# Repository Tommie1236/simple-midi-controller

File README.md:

# Simple MIDI Controller

### A simple 32-button MIDI controller with bank support, built around the RP2040 microcontroller (e.g., RP2040-Zero, but other RP2040 boards should work with appropriate pin changes). Designed for compatibility with any software that accepts USB MIDI input.
## Features

  32 configurable buttons
  Multiple banks for expanded control
  USB MIDI device class (works out-of-the-box with most DAWs and lighting control software)
  MAX7219 7-segment display for bank number
  LVGL graphics library integration for future graphical display support
  Example use: MyDMX, generic macropad for other MIDI-compatible software

## Hardware

  Primary target: RP2040-Zero
  Any RP2040-based board can be used (adjust pin mappings as needed)
  Wiring and assembly instructions: TODO!!

## Software Dependencies

  Raspberry Pi Pico SDK
  TinyUSB
  LVGL v9.4.0 (Light and Versatile Graphics Library)

## Building and Flashing

  Clone this repository and its dependencies.
  Build the firmware using the included build script in the root directory. 
  Optionally use the -l flag to automaticly use picotool to load it to the device.
  Or reboot into bootsel mode and drag the compiled binary(.uf2) onto the usb mass storage device. 

## Usage

Once flashed, the controller will appear as a standard USB MIDI device. It should work with any MIDI-compatible software. Currently tested with MyDMX, but suitable for general MIDI macro control.

For information about the LVGL graphics library integration, see [Code/LVGL_INTEGRATION.md](Code/LVGL_INTEGRATION.md).

Pin Configuration

  Default pin mappings are defined in the code for RP2040-Zero.
  If you use a different RP2040 board, update the pin definitions as needed in the source files.

## Roadmap

  - [x] implement segment display
  - [x] add banking support
  - [x] add LVGL graphics library for future graphical display/menu support
  - [ ] add a menu for configuration?
  - [ ] Add full hardware assembly and wiring instructions
  - [x] create pcb for easier replication without the big amount of soldering perfboard requires.
  - [x] ^ also schematic?
  
## Ai useage (hackclub Summer of Making)
I've used ai in this project. for example to create a base for this readme but i have also used some chatbots with high level debugging if i got stuck.
I've also had copilot enable in vscode when i started the project. but i've since switched to neovim and didn't add any ai or lsp yet. so mostly just high level debugging and writing text. (I'm very bad at this as you can probably already see.)
I really don't like using ai to generate code snippets. sometimes copilot is usefull when you need a lot of repeating code with just a simple parameter changing. But the rest of the time it is pretty useless imo and things like chatgpt/gemini make too many mistakes or inefficiencies to be usefull for snippets.

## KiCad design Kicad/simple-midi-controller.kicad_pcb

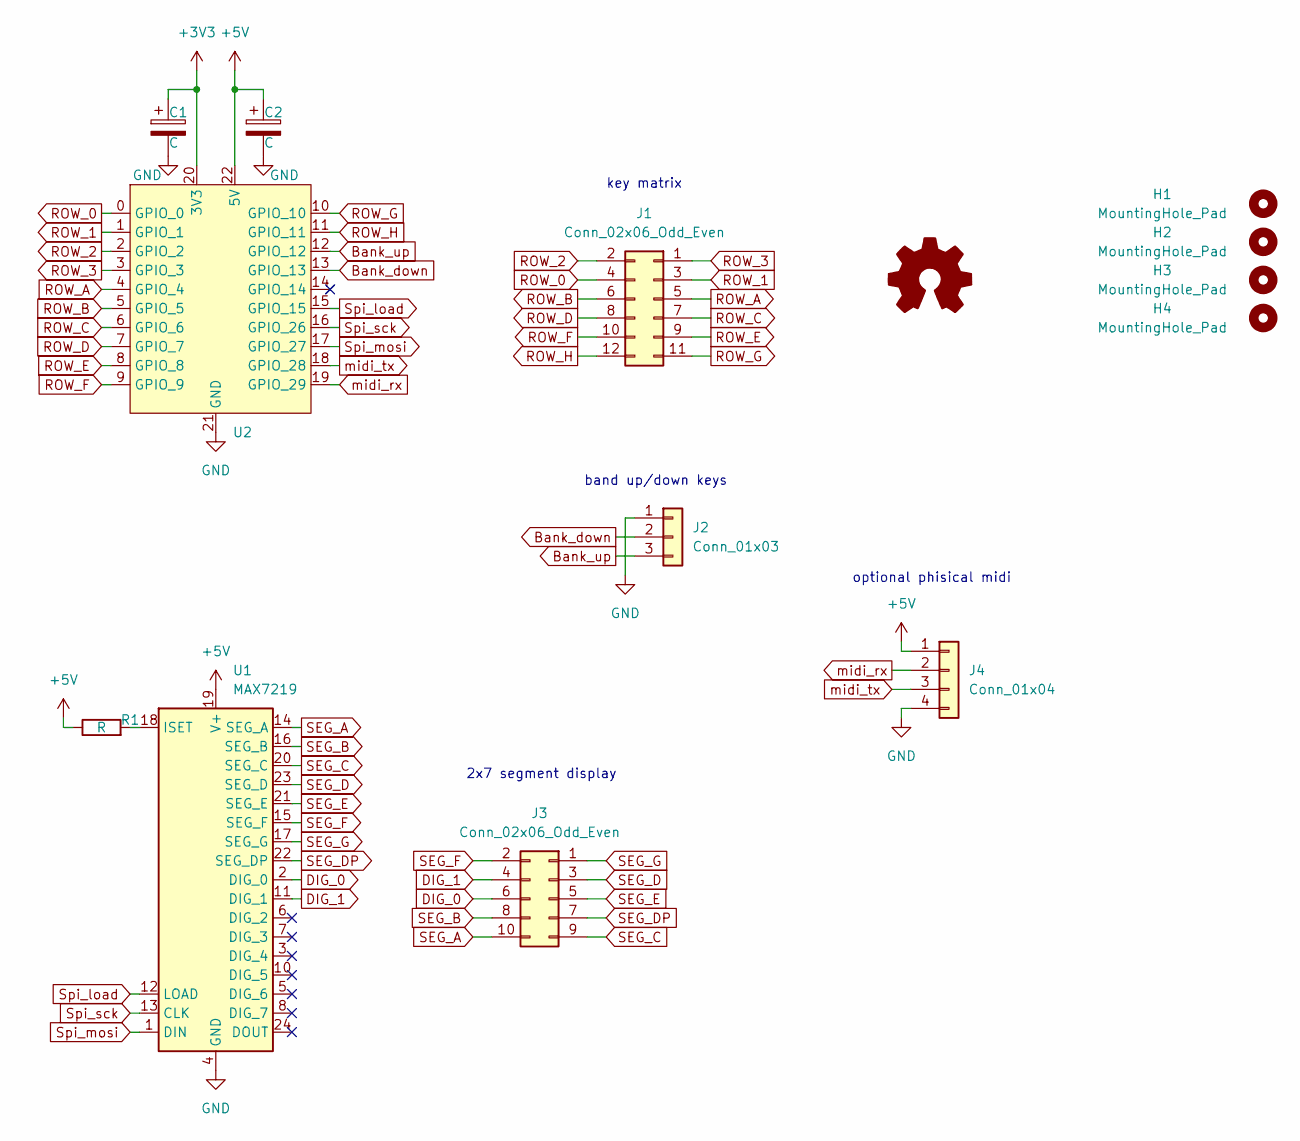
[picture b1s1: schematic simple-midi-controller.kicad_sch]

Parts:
C1, C2: C; CP_Radial_D5.0mm_P2.50mm
H1, H2, H3, H4: MountingHole_Pad; MountingHole_3.2mm_M3
J1: Conn_02x06_Odd_Even; PinHeader_2x06_P2.54mm_Vertical
J2: Conn_01x03; PinHeader_1x03_P2.54mm_Vertical
J3: Conn_02x06_Odd_Even; PinHeader_2x05_P2.54mm_Vertical
J4: Conn_01x04; PinHeader_1x04_P2.54mm_Vertical
R1: R; R_Axial_DIN0207_L6.3mm_D2.5mm_P10.16mm_Horizontal
U1: MAX7219; DIP-24_W7.62mm_Socket
U2: RP2040-Zero

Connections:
+3V3: C1.1, U2.20 (3V3)
+5V: C2.1, J4.1, R1.1, U1.19 (V+), U2.22 (5V)
Bank_down: J2.2, U2.13 (GPIO_13)
Bank_up: J2.3, U2.12 (GPIO_12)
DIG_0: J3.6, U1.2 (DIG_0)
DIG_1: J3.4, U1.11 (DIG_1)
GND: C1.2, C2.2, J2.1, J4.4, U1.4 (GND), U1.9 (GND), U2.21 (GND)
unnamed: R1.2, U1.18 (ISET)
ROW_0: J1.4, U2.0 (GPIO_0)
ROW_1: J1.3, U2.1 (GPIO_1)
ROW_2: J1.2, U2.2 (GPIO_2)
ROW_3: J1.1, U2.3 (GPIO_3)
ROW_A: J1.5, U2.4 (GPIO_4)
ROW_B: J1.6, U2.5 (GPIO_5)
ROW_C: J1.7, U2.6 (GPIO_6)
ROW_D: J1.8, U2.7 (GPIO_7)
ROW_E: J1.9, U2.8 (GPIO_8)
ROW_F: J1.10, U2.9 (GPIO_9)
ROW_G: J1.11, U2.10 (GPIO_10)
ROW_H: J1.12, U2.11 (GPIO_11)
SEG_A: J3.10, U1.14 (SEG_A)
SEG_B: J3.8, U1.16 (SEG_B)
SEG_C: J3.9, U1.20 (SEG_C)
SEG_D: J3.3, U1.23 (SEG_D)
SEG_DP: J3.7, U1.22 (SEG_DP)
SEG_E: J3.5, U1.21 (SEG_E)
SEG_F: J3.2, U1.15 (SEG_F)
SEG_G: J3.1, U1.17 (SEG_G)
Spi_load: U1.12 (LOAD), U2.15 (GPIO_15)
Spi_mosi: U1.1 (DIN), U2.17 (GPIO_27)
Spi_sck: U1.13 (CLK), U2.16 (GPIO_26)
midi_rx: J4.2, U2.19 (GPIO_29)
midi_tx: J4.3, U2.18 (GPIO_28)

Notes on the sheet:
2x7 segment display
optional phisical midi
band up/down keys
key matrix

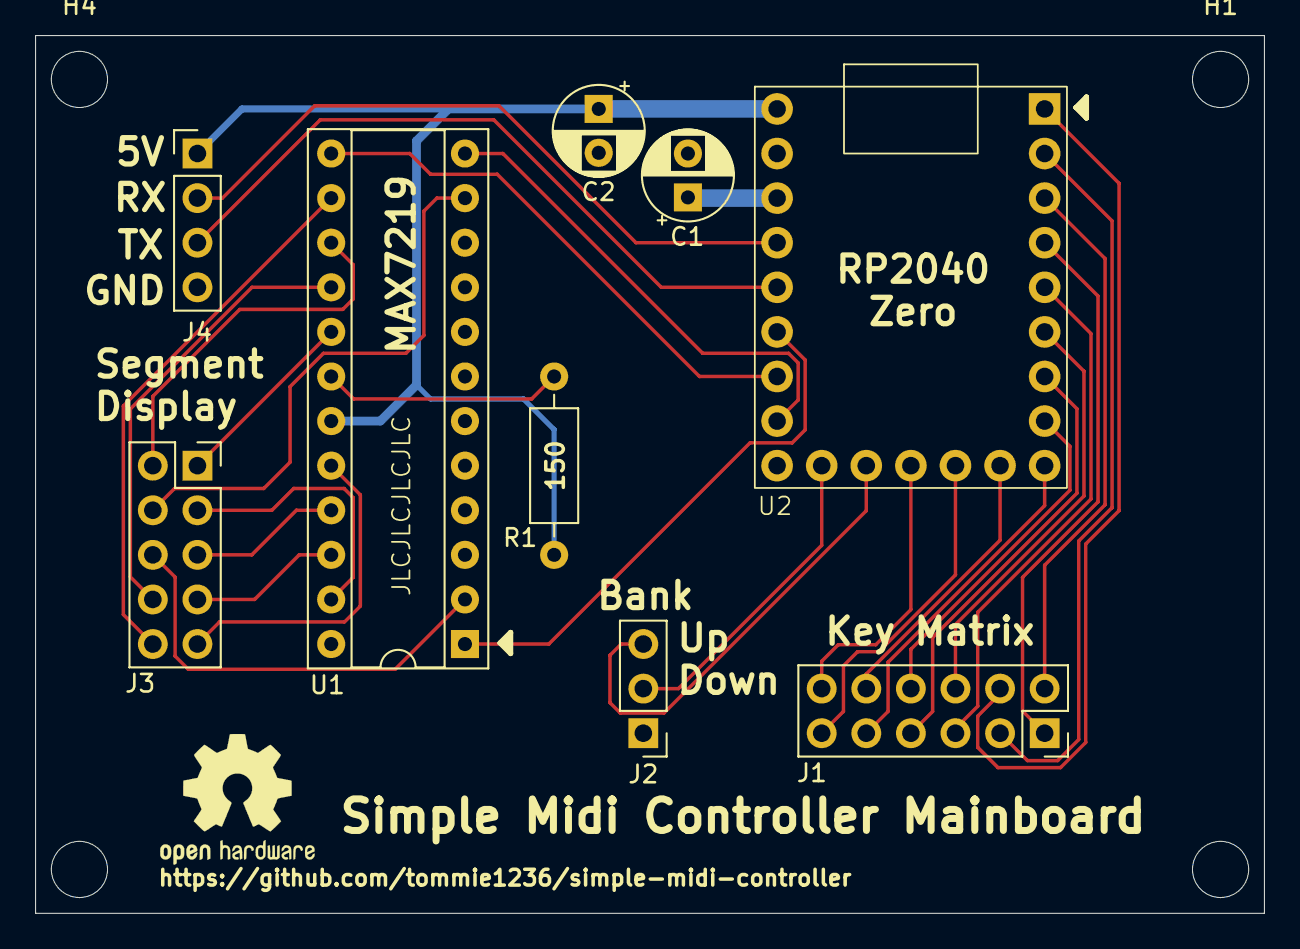
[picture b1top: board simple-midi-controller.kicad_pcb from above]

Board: 2 copper layers, 70.0 x 50.0 mm, 13 parts (0 on the bottom side), 33 nets.

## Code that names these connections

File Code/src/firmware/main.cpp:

#include "main.h"

// rp2040 
#include "pico/stdlib.h"
#include "pico/binary_info.h"
#include "pico/time.h"
#include "pico/multicore.h"
#include "hardware/gpio.h"
#include "hardware/spi.h"

// c/cpp 
#include <unordered_map>

// tinyusb
#include "bsp/board.h"
#include "tusb.h"



void midi_task();
void key_matrix_task();
void segment_display_task();
void init_gpio();
void init_segment_display();
void init_phisical_midi();
void check_debug();

uint8_t current_bank = 0;

uint32_t tud_midi_n_stream_write(uint8_t itf, uint8_t cable_num, uint8_t const* buffer, uint32_t bufsize);  // vscode thinks this isn't defined, but is defined at compile and complies correctly. //TODO: remove when fixed or finished

uint32_t buttons_pressed = 0x00000000;
uint32_t previous_buttons_pressed = 0x00000000;

const uint8_t row_pins[MATRIX_ROWS] =
    {
        ROW_0_PIN,
        ROW_1_PIN,
        ROW_2_PIN,
        ROW_3_PIN
    };

const uint8_t collumn_pins[MATRIX_COLS] =
    {
        COL_A_PIN,
        COL_B_PIN,
        COL_C_PIN,
        COL_D_PIN,
        COL_E_PIN,
        COL_F_PIN,
        COL_G_PIN,
        COL_H_PIN
    };

enum class Debug_Mode {
    PRINT_PRESSED = DEBUG_PRINT_PRESSED,
    DISPLAY_LAST_BUTTON = DEBUG_DISPLAY_LAST_BUTTON,
    CONTINUES_MIDI = DEBUG_CONTINUES_MIDI,
    NUM_DEBUG_MODES
}

std::unordered_map<Debug_Mode, bool> debug_settings;


// TODO: change to new debug modes.
#if DEBUG_PRINT
#define debug_printf(format, ...) \
    do { \
        printf(format, ##__VA_ARGS__); \
    } while (0)
#else
#define debug_printf(format, ...) \
    do {} while (0)
#endif




void core1_main(){
    while (1){
        tud_task();
    }
};

void core0_main(){
    board_init(); 
    tusb_init();
    stdio_usb_init();

    init_gpio();
    // init_segment_display();

    multicore_launch_core1(&core1_main);

    check_debug();

    while(1) {
        key_matrix_task();
        midi_task();
        sleep_ms(1);
        //segment_display_task();
	};
};


int main() {
	
	core0_main();

    return 0;
}



void init_gpio() {
    gpio_init_mask(matrix_out_mask | matrix_in_mask);
    gpio_set_function_masked(matrix_out_mask | matrix_in_mask, GPIO_FUNC_SIO);
	// implement banks later
    //gpio_init(BANK_UP_PIN);
    //gpio_init(BANK_DOWN_PIN);

    gpio_set_dir_in_masked(matrix_in_mask); 
	for (uint pin = 0; pin < 32; ++pin) {
		if (matrix_in_mask & (1u << pin)) {

            // Change to pull down with diodes in correct orientation
			gpio_pull_up(pin);
		}
	}

    gpio_set_dir_out_masked(matrix_out_mask);

    gpio_set_dir(BANK_UP_PIN, GPIO_IN);
    gpio_set_dir(BANK_DOWN_PIN, GPIO_IN); 
    gpio_pull_up(BANK_UP_PIN);
    gpio_pull_up(BANK_DOWN_PIN);

}

void init_segment_display() {
    spi_init(MAX7219_SPI_PORT, 10000 * 1000); // 10MHz

    gpio_set_dir(MAX7219_CS_PIN, GPIO_OUT);
    gpio_set_function(MAX7219_CS_PIN, GPIO_FUNC_SIO);
    gpio_set_function(MAX7219_CLK_PIN, GPIO_FUNC_SPI);
    gpio_set_function(MAX7219_MOSI_PIN, GPIO_FUNC_SPI);
};

void init_phisical_midi () {
    // gpio_set_function(MIDI_TX_PIN, GPIO_FUNC_UART);
    // gpio_set_function(MIDI_RX_PIN, GPIO_FUNC_UART);
};

void check_debug() {
    // read keyboard for debug keys
    key_matrix_task();
    if (buttons_pressed & 1) {
        debug_settings[Debug_Mode::DISPLAY_LAST_BUTTON] = true;
        printf("[DEBUG] DISPLAY_LAST_BUTTON Active");
    } else if (buttons_pressed & (1 << 1)) {
        debug_settings[Debug_Mode::PRINT_PRESSED] = true;
        printf("[DEBUG] PRINT_PRESSED Active");
    } else if (buttons_pressed & (1 << 2)) {
        debug_settings[Debug_Mode::CONTINUES_MIDI] = true;
        printf("[DEBUG] CONTINUES_MIDI Active");
    };
};

void midi_task() {

    uint8_t msg[3];
    uint32_t changed_buttons = buttons_pressed ^ previous_buttons_pressed;
	
    // debug_printf("buttons: %08X \n", int(buttons_pressed));

    msg[0] = 0x90 | (current_bank / 4); 

    for (int i = 0; i < 32; i++) {
        uint32_t mask = 1 << i;

        if (changed_buttons & mask) {
            
            msg[1] = i + ((current_bank % 4) * 32); // Note number TODO: apply bank
            if (buttons_pressed & mask) {
                // Button pressed
                msg[2] = 127; // velocito / on
                debug_printf("Button %d pressed\n", i);
            } else {
                // Button released
                msg[2] = 0; // velocito / off
                debug_printf("Button %d released\n", i);
            }
            tud_midi_n_stream_write(0, 0, msg, 3);
        }

    }

    previous_buttons_pressed = buttons_pressed;
}


static bool bank_up_last = true;
static bool bank_down_last = true;

void key_matrix_task() {

    bool bank_up_current = gpio_get(BANK_UP_PIN);
    bool bank_down_current = gpio_get(BANK_DOWN_PIN);

    if (!bank_up_current & bank_up_last) {
        if (current_bank == 63) {
            current_bank = 0;
        } else {
            current_bank++;
        }
    }

    if (!bank_down_current & bank_down_last) {
        if (current_bank == 0) {
            current_bank = 63;
        } else {
            current_bank--;
        }
    }

    bank_up_last = bank_up_current;
    bank_down_last = bank_down_current;


    buttons_pressed = 0;

    for ( int row_idx = 0; row_idx < MATRIX_ROWS; ++row_idx) {
        
        gpio_set_mask(matrix_out_mask);

        gpio_put(row_pins[row_idx], 0);
        sleep_us(50);

        uint32_t gpio_state = gpio_get_all();

        for (int collumn = 0; collumn < MATRIX_COLS; ++collumn) {
            uint8_t pin = collumn_pins[collumn];
        }
    }
}

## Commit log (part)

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2024-12-25 started model and project
2024-12-26 almost finished faceplate.
    realised it won't fit in my printer so need to redesign
2024-12-26 finished faceplate for real
2025-01-06 added pico sdk
2025-01-06 started code
2025-01-07 should now have working matrix scanning and basic midi transmitting
2025-01-07 updated model
2025-01-29 moved double const var def to header file
2025-02-20 fixed key matrix scanning and broke midi
2025-02-25 tried some more but usb not worky worky on win
2025-05-18 disabled blocking matrix scanning code and fixed usb connection for windows
2025-05-18 fixed pinout diagram
2025-05-18 reimplemented matrix scanning and usb together
2025-05-25 should have optimized matrix scans. NOT TESTED
    don't have the hardware with me but this should work
2025-06-04 replaced forgotten temp var from so
2025-06-18 fixed pullup
2025-06-18 rewrote matrix scanning again and it is tested and working now
2025-06-18 fixed typo. 30->32
2025-06-19 put debug logs behind a debug define in main.h
2025-06-19 fixed windows freezes and changed device name to something proper
2025-06-19 basic midi channel selection through define in main.h.
    better implementation later
2025-06-20 removed some forgotten deprecated code
2025-06-21 moved some init for pheripherals to separate init methods
2025-06-22 added base code for debug modes
2025-06-22 fixed typo's
2025-06-23 added continues midi debug mode
2025-06-23 fixed typo continues -> continuous
2025-06-23 changed unordered map with c style array and fixed some bugs
2025-06-24 this should fix debug modes but i broke the hardware so can't reliably test
2025-06-25 small comment edits
2025-06-25 created pcb
2025-06-25 add hackatime badge to readme
2025-06-26 converted project to c. idk why
2025-06-27 added bank support to midi
2025-06-27 fixed duplicate bank variable
2025-06-27 Update roadmap
2025-06-27 updated pcb design
2025-06-28 reworked bank switching
2025-06-29 added build test action
2025-06-29 upload artifact by gh action
2025-06-29 think i fixed bug in actifact upload of gh action
2025-06-30 merged main back into flex io mapping
2025-06-30 fixed broken merge commit
2025-07-09 fixed wireing and updated header
2025-07-11 first version of segment driver working
2025-07-11 started flexible mapping
2025-07-12 now very working led driver and integrated it into the main code
2025-07-13 started on phy midi and just made code more readable etc
2025-07-13 bunch of small fixes/improvements and optimizations
2025-12-30 Initial plan
2025-12-30 Add LVGL library support with basic display driver and UI
2025-12-30 Fix spelling errors and documentation inconsistencies
2025-12-30 Add LVGL graphics library support
